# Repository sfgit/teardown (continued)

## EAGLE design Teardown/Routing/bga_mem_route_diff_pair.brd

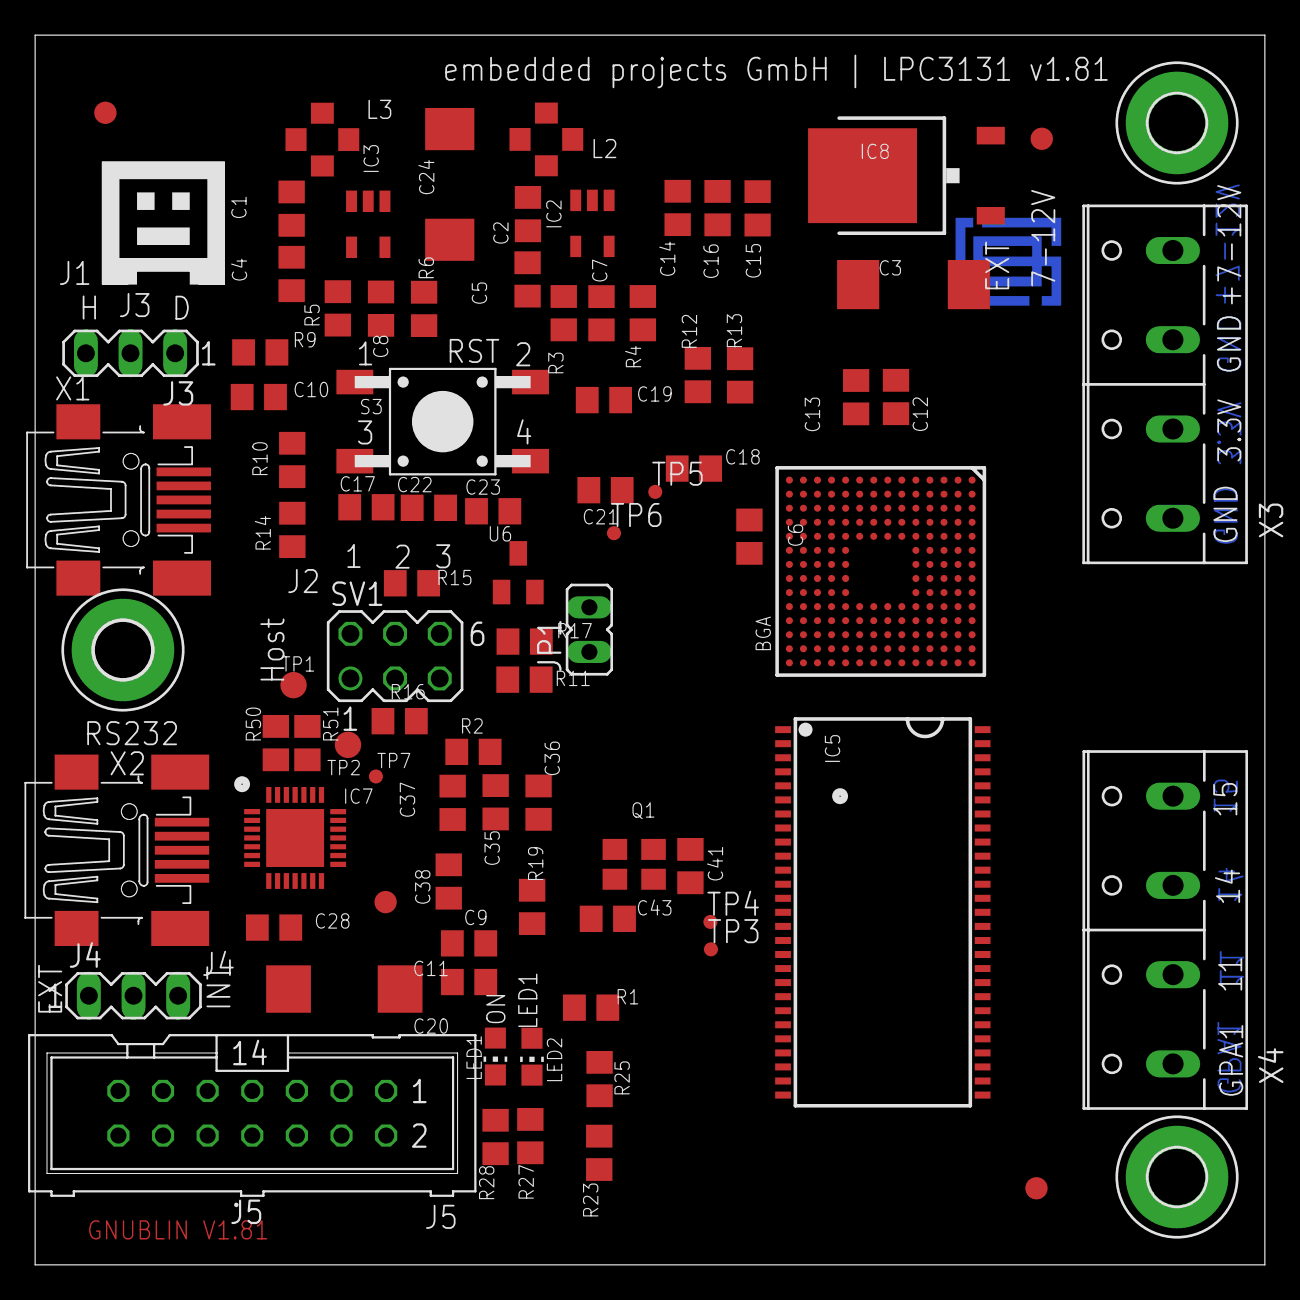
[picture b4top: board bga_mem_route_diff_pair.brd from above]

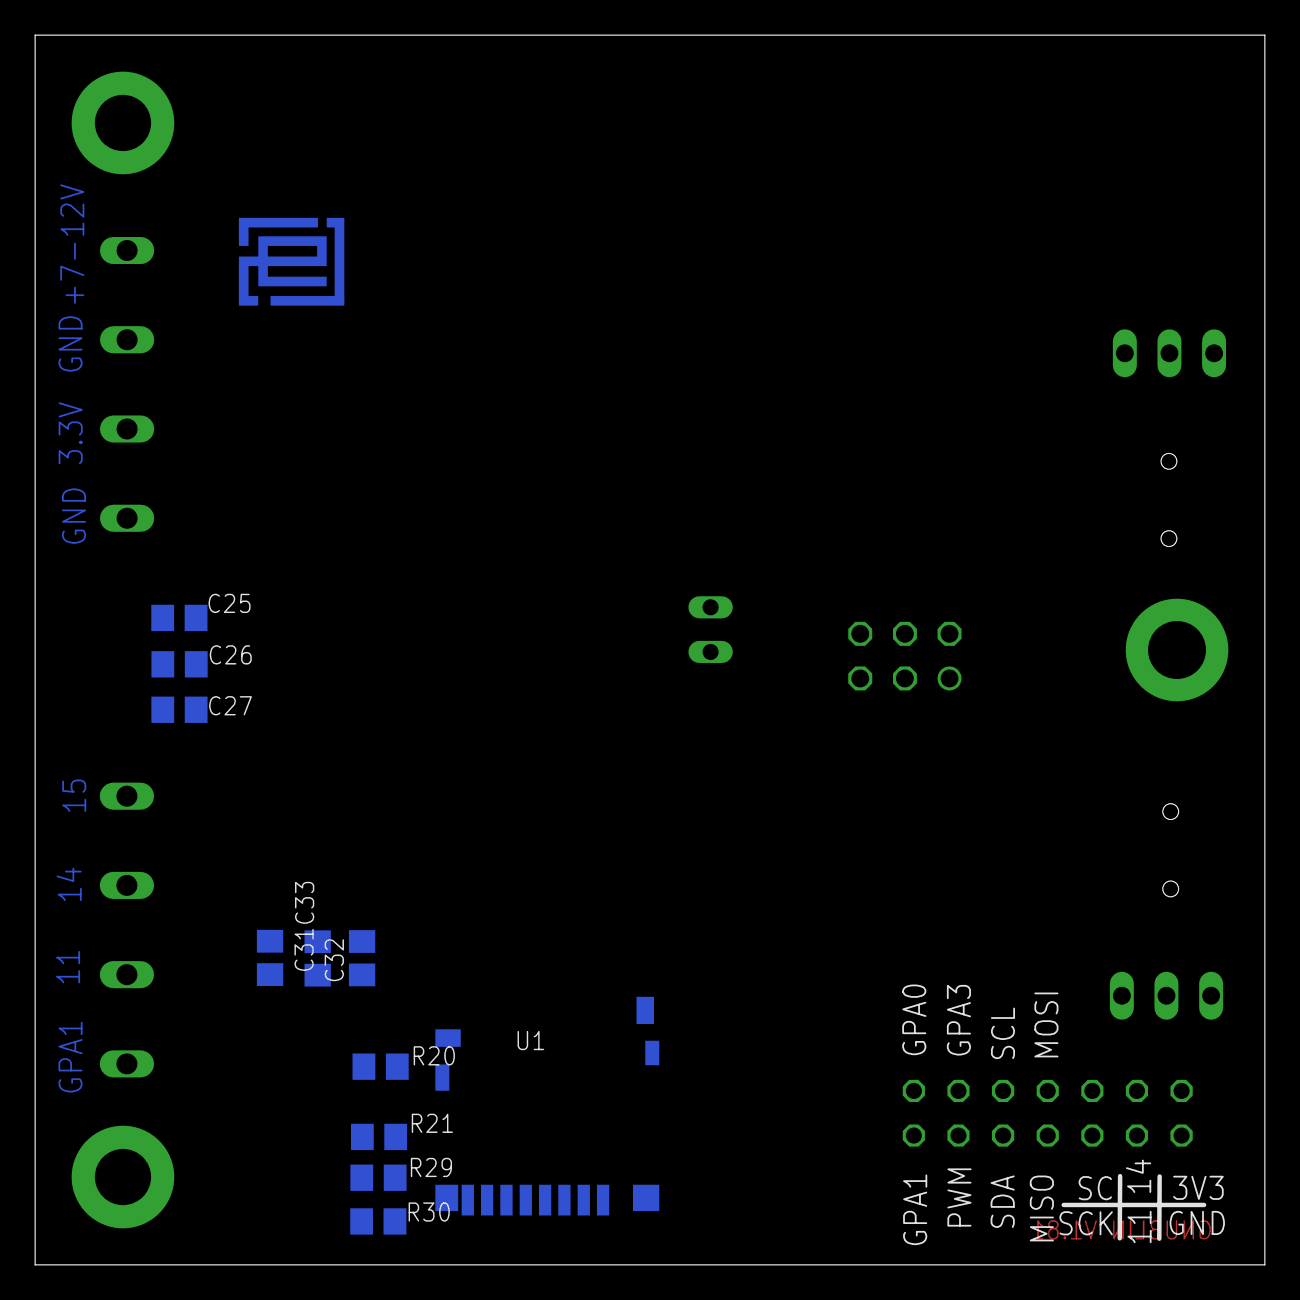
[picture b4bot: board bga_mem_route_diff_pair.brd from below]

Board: 4 copper layers, 70.0 x 70.0 mm, 102 parts (12 on the bottom side), 70 nets, no tracks yet.

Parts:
BGA: LPC313XFET180; TFBGA180
C1, C2, C11, C13, C14, C21, C23, C27, C32, C37: 10uF; C0805
C3, C24: 10uF; SMC_D
C4, C5: 4.7uF; C0805
C6, C9, C10, C16, C18, C22, C26, C33, C35, C38: 100nF; C0805
C7, C8, C41, C43: 22pF; C0805
C12, C15, C17, C19, C25, C31, C36: 3.3nF; C0805
C20: 10uF; D/7343-31R
C28: 2.2uF; C0805
FID1, FID2, FID3, FID4: PASSERMARKEN_FIDUCIAL
H1, H4: MOUNT-PAD-ROUND3.2; 3,2-PAD
H2: MOUNT-PAD-ROUND3.3; 3,3-PAD
IC2, IC3: AS1324; TSOT23
IC5: A43E26161TSOPII; TSOPII
IC7: CP21021; MLP28
IC8: MC78M05ABDT; DPACK_3
J3, J4: MA03-1
J5: ML14
JP1: JP1
L2, L3: 4u7; PSU3014
LED1: GRUEN; CHIP-LED0805
LED2: ROT; CHIP-LED0805
Q1: SX-32 12.000 MHz; SX-32
R1, R2, R9, R12, R15, R16, R17, R20, R21, R23, R25, R29, R30: 10K; R0805
R3, R4, R5: 301K; R0805
R6: 66K5; R0805
R10, R14: 1M; R0805
R11: 12K 1%; R0805
R13: DNP; R0805
R19: 22R; R0805
R27, R28: 270R; R0805
R50, R51: 0R; R0805
S3: TASTER-9314_SMD
SV1: MA03-2
TP1, TP2: TPTP15R; TP15R
TP3, TP4: PTR1TP08R; TP08R
TP5, TP6, TP7: TPTP08R; TP08R
U1: DM3D-SF
U6: APX803; SOT23
U$3: GNUBLINLOGOSIEB; GNUSIEBDRUCK
U$4: EPLOGO; EPLOGOKUPFER
X1, X2: MINI-USB-32005-201; 32005-201
X3, X4: W237-4P

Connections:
5V: C4.1, C5.1, C20.+, C24.+, C28.1, IC2.1, IC2.4, IC3.1, IC3.4, IC7.7, IC7.8, J3.3, J4.2
+1V2: BGA.A9, BGA.C6, BGA.C9, BGA.C12, BGA.D11, BGA.E10, BGA.H3, BGA.L1, BGA.L7, BGA.L12, C2.2, C7.1, C18.2, C19.2, C21.2, L2.2, R3.2
+5V_USB: J4.3, X2.1
+7-12V: C3.+, IC8.1, X3.4
CLK_00: BGA.K14, C25.2, C26.2, C27.2, IC5.14, IC5.43, IC5.49, X3.2
D+: IC7.4, X2.3
D-: IC7.5, X2.2
EXT_5V: IC8.3, J4.1
GND: BGA.A11, BGA.A12, BGA.B12, BGA.C3, BGA.C4, BGA.C7, BGA.D6, BGA.D8, BGA.D9, BGA.D12, BGA.E4, BGA.E9, BGA.F4, BGA.G4, BGA.G11, BGA.H4, BGA.K3, BGA.K4, BGA.L3, BGA.L6, BGA.L9, BGA.L11, BGA.M3, BGA.M4, BGA.M6, BGA.M8, BGA.N1, C1.1, C2.1, C3.-, C4.2, C5.2, C6.1, C10.1, C12.1, C13.1, C14.1, C15.1, C16.1, C17.1, C18.1, C19.1, C21.1, C22.1, C23.1, C24.-, IC2.2, IC3.2, IC8.4, JP1.1, R4.1, R6.1, R10.1, R11.1, R13.1, R14.1, S3.3, S3.4, SV1.1, SV1.2, U6.1, X1.5
GPIO0: BGA.K10, R15.1
LPC_A0: BGA.B3, IC5.23
LPC_A1: BGA.A2, IC5.24
LPC_A6: BGA.K6, IC5.31
LPC_A9: BGA.L5, IC5.34
LPC_A12: BGA.K5, IC5.36
LPC_DM: BGA.N2, R10.2, X1.2
LPC_DP: BGA.P2, R14.2, X1.3
LPC_MCI_CD: R20.2, U1.SW_A
LPC_MCI_CMD: R29.2, U1.3
LPC_MCI_DAT0: R25.2, U1.7
LPC_MCI_DAT1: R23.2, U1.8
LPC_MCI_DAT2: BGA.C5, R30.2, U1.1
LPC_MCI_DAT3: BGA.A4, R21.2, U1.2
LPC_RXD: BGA.P12, R50.2, TP1.TP
LPC_TXD: BGA.N12, R51.2, TP2.TP
LPC_VBUS: C10.2, J3.1, R9.1
MEM_A1_N: BGA.P13, IC5.2
MEM_A1_P: BGA.P14, IC5.1
MEM_A2_N: BGA.N13, IC5.4
MEM_A2_P: BGA.N14, IC5.3
MEM_A3_N: BGA.M13, IC5.6
MEM_A3_P: BGA.M14, IC5.5
MEM_A4_N: BGA.L13, IC5.8
MEM_A4_P: BGA.L14, IC5.7
MEM_A5_N: BGA.J13, IC5.11
MEM_A5_P: BGA.J14, IC5.10
MEM_A6_N: BGA.A13, IC5.53
MEM_A6_P: C25.1, C26.1, C27.1, C31.1, C32.1, C33.1, IC5.12, IC5.28, IC5.41, X3.1, X3.3
MEM_A7_N: BGA.B13, IC5.51
MEM_A7_P: BGA.B14, IC5.52
MEM_A8_N: BGA.B2, BGA.D5, BGA.D7, BGA.E5, BGA.E8, BGA.F5, BGA.G5, BGA.G12, BGA.H5, BGA.K11, BGA.L4, BGA.L10, BGA.M2, BGA.M5, BGA.M7, BGA.M9, C1.2, C8.1, C17.2, C22.2, C23.2, C31.2, C32.2, C33.2, IC5.27, IC5.47, J5.13, L3.2, LED1.A, R1.2, R2.1, R5.2, R17.2, R19.1, R20.1, R21.1, R23.1, R25.1, R29.1, R30.1, SV1.5, SV1.6, U1.4, U6.3
MEM_A8_P: BGA.C14, IC5.48
MEM_A9_N: BGA.D13, IC5.45
MEM_A9_P: BGA.D14, IC5.46
unnamed: IC7.26, R50.1
unnamed: IC7.25, R51.1
unnamed: LED2.C, R27.2
unnamed: LED1.C, R28.2
unnamed: IC2.3, L2.1
unnamed: BGA.N11, R12.1, R13.2
unnamed: J3.2, X1.1
unnamed: R1.1, TP3.TP
unnamed: IC7.24, TP7.TP
unnamed: BGA.J10, R2.2
unnamed: R15.2, SV1.4
unnamed: R16.1, SV1.3
unnamed: C7.2, IC2.5, R3.1, R4.2
unnamed: C9.2, C11.2, R19.2
unnamed: BGA.J5, R11.2
unnamed: BGA.L2, R9.2
unnamed: IC3.3, L3.1
unnamed: C8.2, IC3.5, R5.1, R6.2
RESET: R17.1, S3.2, U6.2
S$2: C6.2, C12.2, C13.2, C14.2, C15.2, C16.2, R12.2
S$4: C35.2, C36.2, C37.2, C38.2
S$5: C41.1, C43.1, U1.6, U1.SW_B
S$6: C9.1, C11.1, C20.-, C28.2, C35.1, C36.1, C37.1, C38.1, IC7.3, IC7.EXP, J5.14, R27.1, R28.1, X2.5
USB_ID: BGA.M1, JP1.2, X1.4
XTAL1: C43.2, Q1.3
XTAL2: C41.2, Q1.1
